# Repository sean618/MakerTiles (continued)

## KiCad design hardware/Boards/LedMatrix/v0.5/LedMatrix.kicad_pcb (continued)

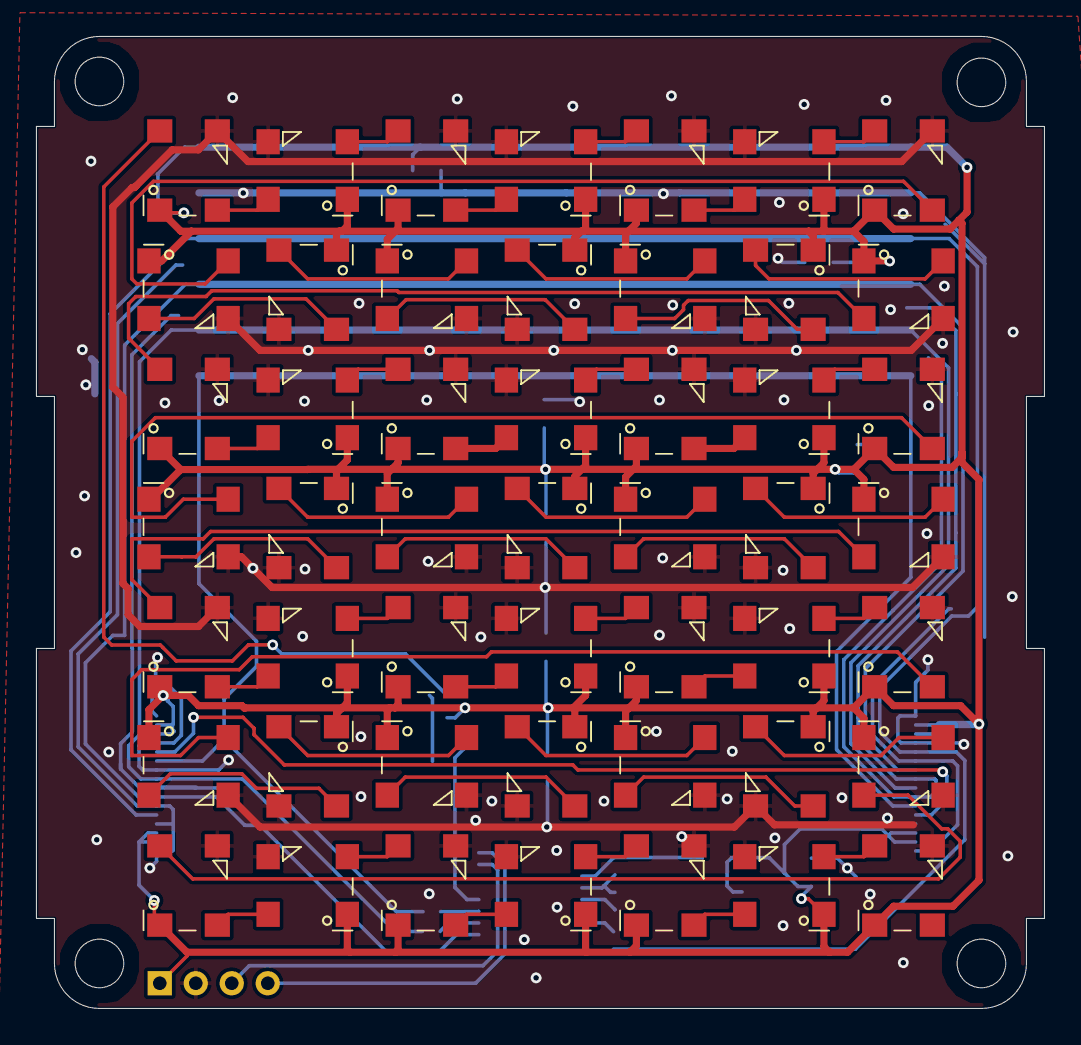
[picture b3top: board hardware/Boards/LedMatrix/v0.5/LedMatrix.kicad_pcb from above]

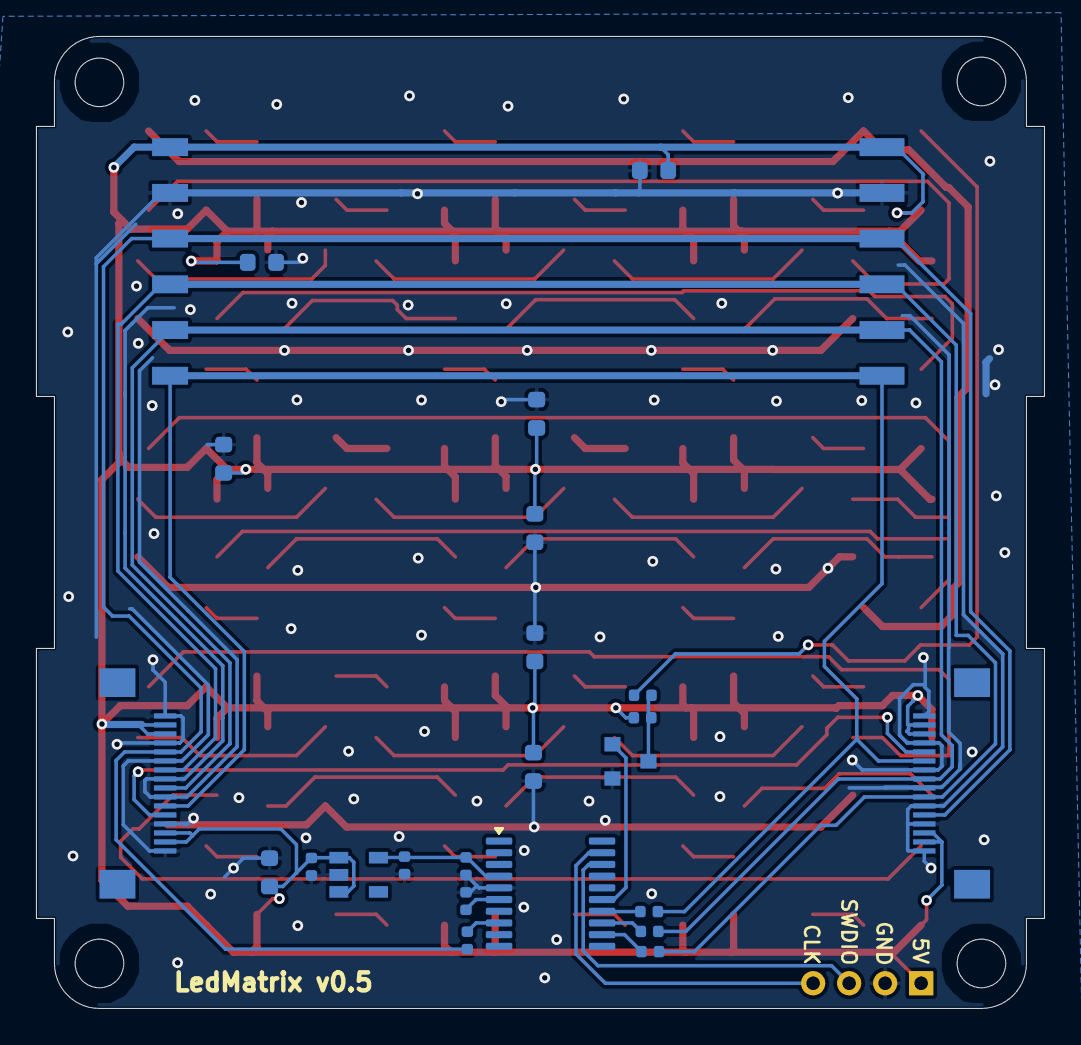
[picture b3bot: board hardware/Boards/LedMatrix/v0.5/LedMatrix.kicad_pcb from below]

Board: 4 copper layers, 56.0 x 54.0 mm, 80 parts (25 on the bottom side), 66 nets.

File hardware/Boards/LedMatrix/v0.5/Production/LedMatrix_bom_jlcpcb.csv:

Comment,Designator,Footprint,LCSC Part Number
WS2812B,"D52,D34,D48,D12,D61,D2,D64,D53,D55,D56,D37,D47,D59,D39,D42,D11,D51,D3,D54,D18,D16,D15,D63,D29,D50,D17,D58,D38,D28,D4,D36,D43,D21,D14,D26,D24,D8,D22,D40,D32,D6,D62,D10,D49,D44,D41,D35,D31,D33,D20,D30,D46,D9,D27,D13,D60,D23,D1,D25,D19,D57,D7,D5,D45",LED_WS2812B_PLCC4_5.0x5.0mm_P3.2mm,C2843785
N_MOSFET,Q1,SOT-23,C8545
STM32G030F6P6,U2,TSSOP-20_4.4x6.5mm_P0.65mm,C529330
FFC_connector_16p_hinge_lock,"J4,J5",FFC_connector_16p_hinge_lock,C262665
22uF_10V,"C8,C6,C11,C15,C16,C7,C13,C12",C_0603_1608Metric,C86295
4.7uF,"C3,C2,C1",C_0402_1005Metric,C23733
75R,"R1,R3,R5,R6",R_0402_1005Metric,C25133
1K,"R4,R2",R_0402_1005Metric,C11702
01x06_2.54mm_Male,J1,01x06_2.54mm_Male,C5242199
0.1uF,C4,C_0402_1005Metric,C1525
ME6211C33M5G-N,U1,SOT-23-5,C81233
01x06_2.54mm_Female,J2,01x06_2.54mm_Female,C5142239

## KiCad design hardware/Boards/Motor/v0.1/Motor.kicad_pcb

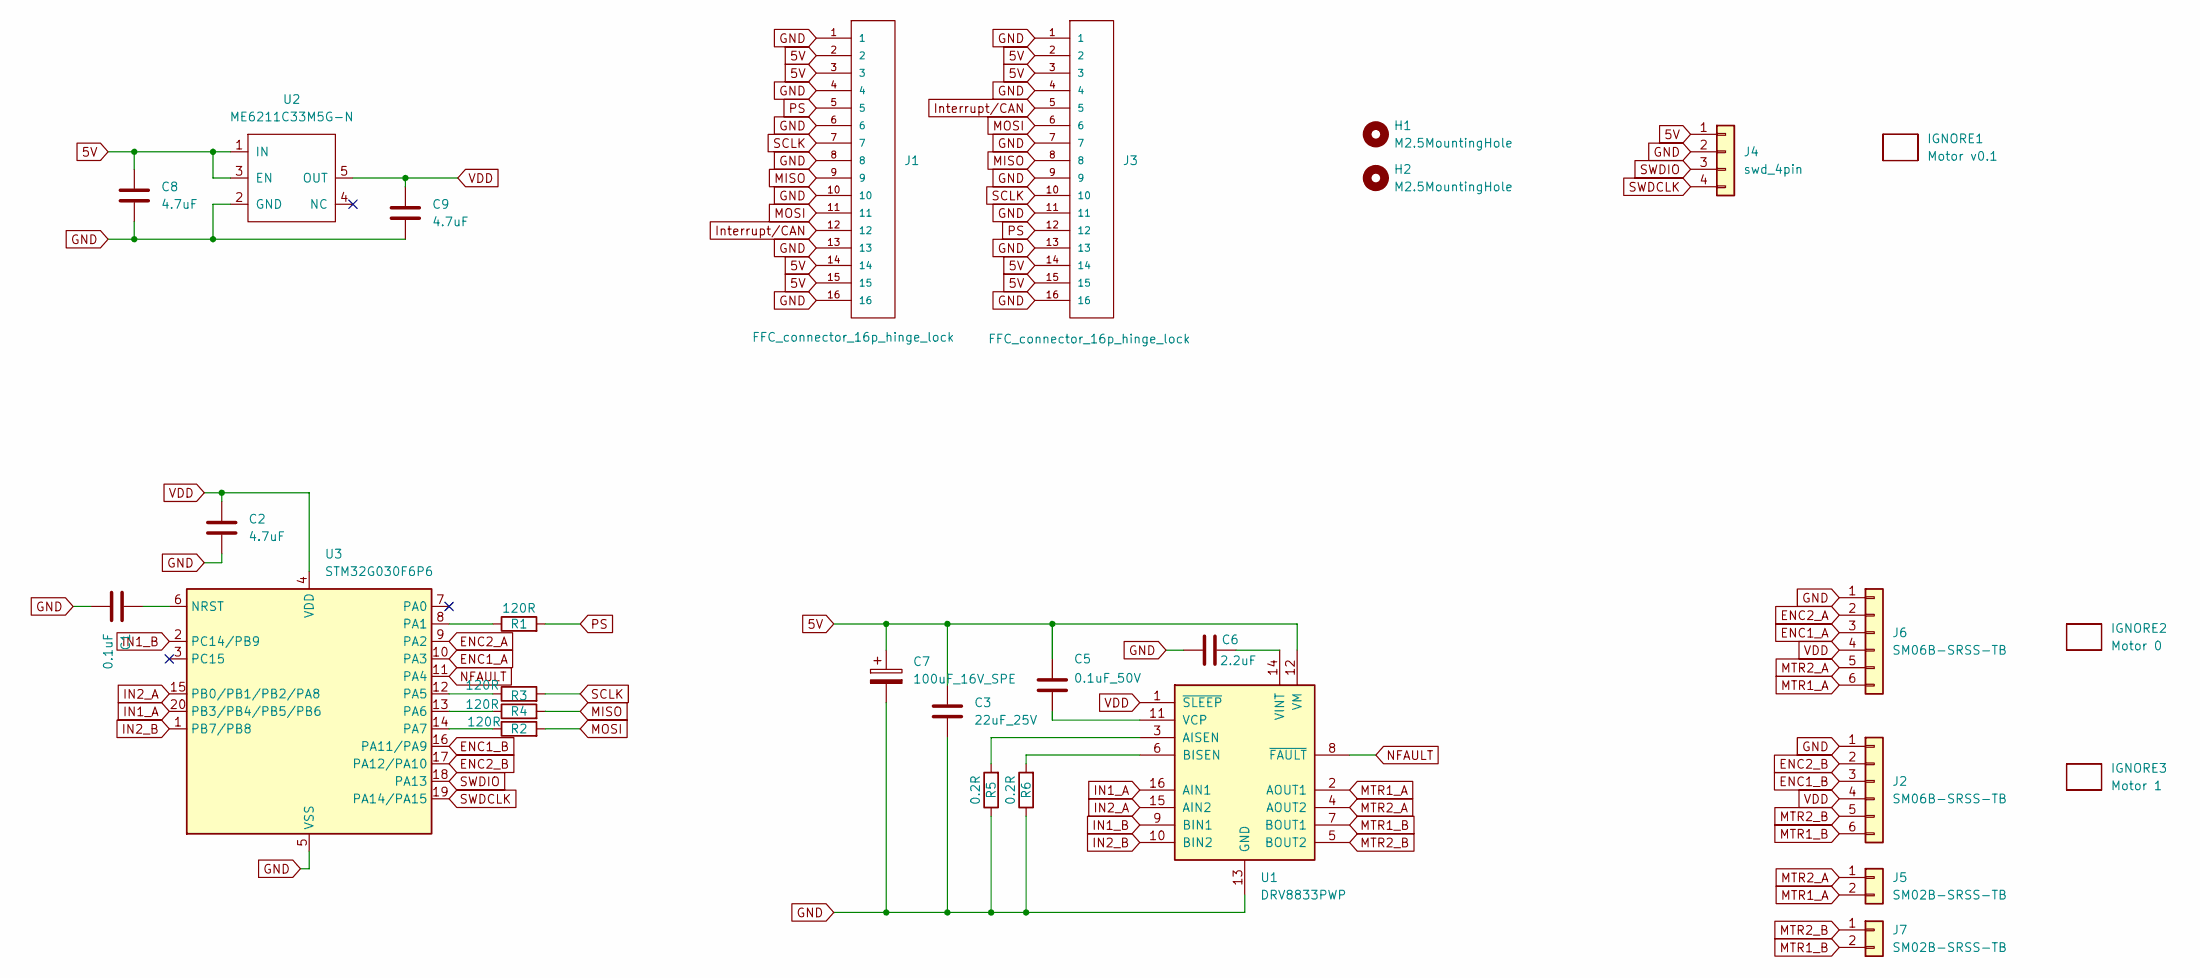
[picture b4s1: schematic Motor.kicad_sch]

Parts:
C1: 0.1uF; C_0402_1005Metric
C2, C8, C9: 4.7uF; C_0402_1005Metric
C3: 22uF_25V; C_0805_2012Metric
C5: 0.1uF_50V; C_0402_1005Metric
C6: 2.2uF; C_0402_1005Metric
C7: 100uF_16V_SPE; CP_Elec_6.3x5.3
H1, H2: M2.5MountingHole; MountingHole_2.7mm_M2.5_ISO7380
IGNORE1: Motor v0.1; BoardText
IGNORE2: Motor 0; BoardText
IGNORE3: Motor 1; BoardText
J1, J3: FFC_connector_16p_hinge_lock
J2, J6: SM06B-SRSS-TB; JST_SH_SM06B-SRSS-TB_1x06-1MP_P1.00mm_Horizontal
J4: swd_4pin; swd_header
J5, J7: SM02B-SRSS-TB; JST_SH_SM02B-SRSS-TB_1x02-1MP_P1.00mm_Horizontal
R1, R2, R3, R4: 120R; R_0402_1005Metric
R5, R6: 0.2R; R_1210_3225Metric
U1: DRV8833PWP; HTSSOP-16-1EP_4.4x5mm_P0.65mm_EP3.4x5mm_Mask2.46x2.31mm_The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
U2: ME6211C33M5G-N; SOT-23-5
U3: STM32G030F6P6; TSSOP-20_4.4x6.5mm_P0.65mm

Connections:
5V: C3.1, C5.1, C7.1, C8.1, J1.2, J1.3, J1.14, J1.15, J3.2, J3.3, J3.14, J3.15, J4.1, U1.12 (VM), U2.1 (IN), U2.3 (EN)
ENC1_A: J6.3, U3.10 (PA3)
ENC1_B: J2.3, U3.16 (PA11/PA9)
ENC2_A: J6.2, U3.9 (PA2)
ENC2_B: J2.2, U3.17 (PA12/PA10)
GND: C1.2, C2.2, C3.2, C6.1, C7.2, C8.2, C9.2, J1.1, J1.4, J1.6, J1.8, J1.10, J1.13, J1.16, J2.1, J3.1, J3.4, J3.7, J3.9, J3.11, J3.13, J3.16, J4.2, J6.1, R5.1, R6.1, U1.13 (GND), U1.17 (GND), U2.2 (GND), U3.5 (VSS)
IN1_A: U1.16 (AIN1), U3.20 (PB3/PB4/PB5/PB6)
IN1_B: U1.9 (BIN1), U3.2 (PC14/PB9)
IN2_A: U1.15 (AIN2), U3.15 (PB0/PB1/PB2/PA8)
IN2_B: U1.10 (BIN2), U3.1 (PB7/PB8)
Interrupt/CAN: J1.12, J3.5
MISO: J1.9, J3.8, R4.2
MOSI: J1.11, J3.6, R2.2
MTR1_A: J5.2, J6.6, U1.2 (AOUT1)
MTR1_B: J2.6, J7.2, U1.7 (BOUT1)
MTR2_A: J5.1, J6.5, U1.4 (AOUT2)
MTR2_B: J2.5, J7.1, U1.5 (BOUT2)
NFAULT: U1.8 (~FAULT), U3.11 (PA4)
unnamed: R5.2, U1.3 (AISEN)
unnamed: R6.2, U1.6 (BISEN)
unnamed: C5.2, U1.11 (VCP)
unnamed: C6.2, U1.14 (VINT)
unnamed: C1.1, U3.6 (NRST)
unnamed: R1.1, U3.8 (PA1)
unnamed: R3.1, U3.12 (PA5)
unnamed: R4.1, U3.13 (PA6)
unnamed: R2.1, U3.14 (PA7)
PS: J1.5, J3.12, R1.2
SCLK: J1.7, J3.10, R3.2
SWDCLK: J4.4, U3.19 (PA14/PA15)
SWDIO: J4.3, U3.18 (PA13)
VDD: C2.1, C9.1, J2.4, J6.4, U1.1 (~SLEEP), U2.5 (OUT), U3.4 (VDD)

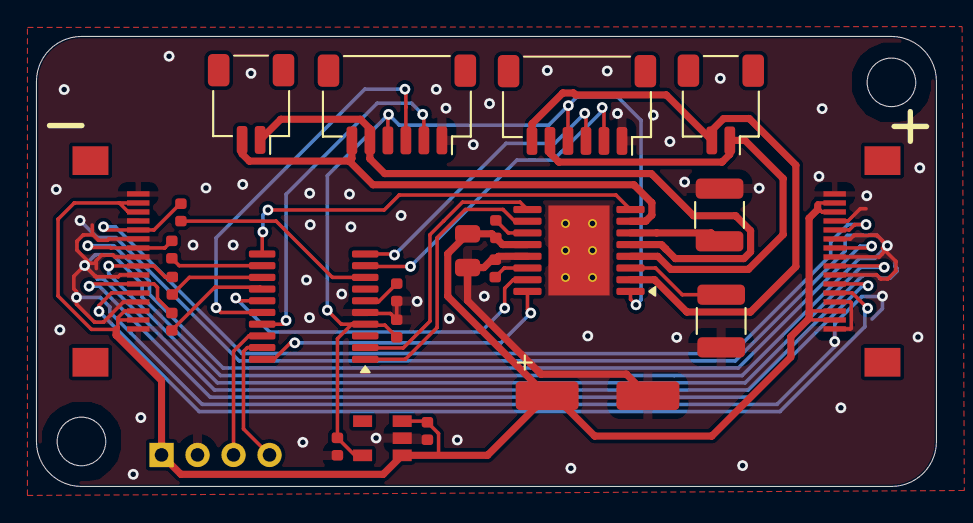
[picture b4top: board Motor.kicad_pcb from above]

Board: 2 copper layers, 50.0 x 25.0 mm, 27 parts (0 on the bottom side), 32 nets.

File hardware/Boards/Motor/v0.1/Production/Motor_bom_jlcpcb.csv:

Comment,Designator,Footprint,LCSC Part Number
4.7uF,"C9,C8,C2",C_0402_1005Metric,C23733
DRV8833PWP,U1,HTSSOP-16-1EP_4.4x5mm_P0.65mm_EP3.4x5mm_Mask2.46x2.31mm_ThermalVias,C50506
FFC_connector_16p_hinge_lock,"J1,J3",FFC_connector_16p_hinge_lock,C262665
0.1uF_50V,C5,C_0402_1005Metric,C77020
SM06B-SRSS-TB,"J2,J6",JST_SH_SM06B-SRSS-TB_1x06-1MP_P1.00mm_Horizontal,C160405
22uF_25V,C3,C_0805_2012Metric,C602037
SM02B-SRSS-TB,"J5,J7",JST_SH_SM02B-SRSS-TB_1x02-1MP_P1.00mm_Horizontal,C160402
ME6211C33M5G-N,U2,SOT-23-5,C81233
120R,"R2,R3,R4,R1",R_0402_1005Metric,C25079
100uF_16V_SPE,C7,CP_Elec_6.3x5.3,C494511
STM32G030F6P6,U3,TSSOP-20_4.4x6.5mm_P0.65mm,C529330
0.1uF,C1,C_0402_1005Metric,C1525
2.2uF,C6,C_0402_1005Metric,C12530
0.2R,"R5,R6",R_1210_3225Metric,C52362
